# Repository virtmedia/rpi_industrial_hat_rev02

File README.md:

# rpi_industrial_hat_rev02
Raspberry Pi hat with industrial-style 2xDI+2xDQ+1W

## Features:
- power supply input 10-26 V with fuse protection, overvoltage protection and reverse polarity protection
- possible to set low voltage level eg. to protect 12V baterry from draining.
- 2 relays for outputs (both NO and NC contacts accesible)
- 2 optocouplers for inputs (can be used SMD or THT versions in 4-pin package)
- 3-pin connector for 1-Wire devices (eg. D18B20 thermometers)
- terminal blocks connectors
- UART conenctor
- I2C connector
- Domoticz and Home Assistant friendly

## Signals used from Raspberry Pi GPIO connector:
- GPIO04: 1-wire
- GPIO17: Relay #2
- GPIO18: Relay #1
- GPIO22: Input #1
- GPIO27: Input #2

Photo of the board (revision 01 with some small mistake, corrected in current revision):

I've included:
- Schematic in PDF
- Board visualisation in PDF
- Gerber files in .zip ready to be send to PCB manufacturer
- Eagle files

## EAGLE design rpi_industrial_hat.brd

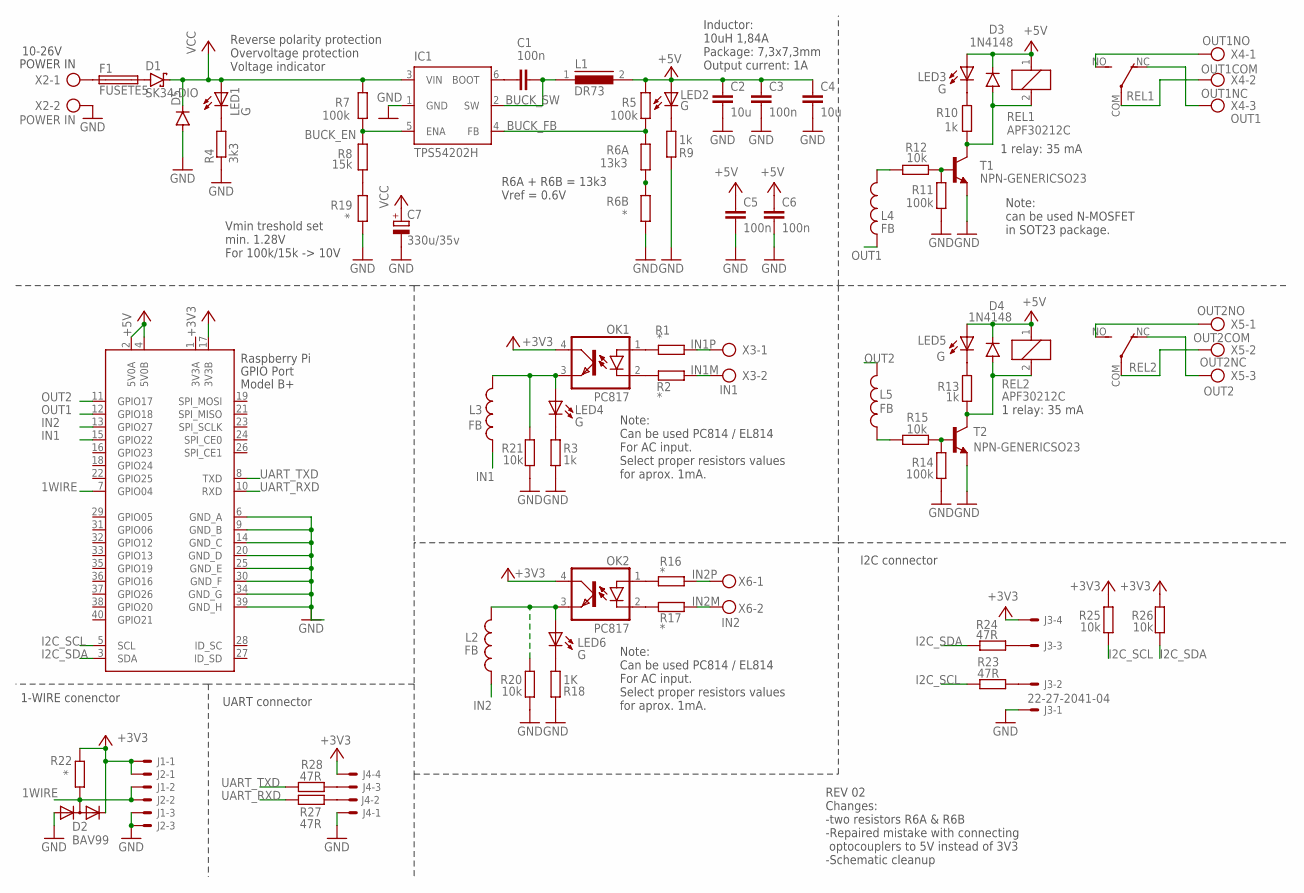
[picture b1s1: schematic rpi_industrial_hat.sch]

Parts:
C1, C3, C5, C6: 100n; C0603
C2, C4: 10u; C0805
C7: 330u/35v; E5-10,5
D1: SK34-DIO; SMC
D2: BAV99; SOT23
D3, D4: 1N4148; MINIMELF
D5: DIODE-DO214AA; DO214AA
F1: FUSETE5; TE5
IC1: TPS54202H; SOT23-6
J1, J2: 22-27-2031-03; 6410-03
J3, J4: 22-27-2041-04; 6410-04
L1: DR73
L2, L3, L4, L5: FB; 0603
LED1, LED2, LED3, LED4, LED5, LED6: G; CHIP-LED0603
OK1, OK2: PC817; DIL04
R1, R2, R16, R17: *; 0204/7/SMD
R3, R9, R10, R13: 1k; R0603
R4: 3k3; R0603
R5, R7, R11, R14: 100k; R0603
R6A: 13k3; R0603
R6B, R19, R22: *; R0603
R8: 15k; R0603
R12, R15, R20, R21, R25, R26: 10k; R0603
R18: 1K; R0603
R23, R24, R27, R28: 47R; R0603
REL1, REL2: APF30212C
T1, T2: NPN-GENERICSO23; SOT23
X1: RASPI_BOARD_B+#_E4P; RASPI_BOARD_B+_EDGES_4DRILL_PAD
X2: POWER IN; AK500/2
X3: IN1; AK500/2
X4: OUT1; AK500/3
X5: OUT2; AK500/3
X6: IN2; AK500/2

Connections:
1WIRE: D2.3 (K1A2), J1.2, J2.2, R22.1, X1.7 (GPIO04)
3V3A: X1.1 (3V3A)
+3V3: D2.2 (K2), J1.1, J2.1, J3.4, J4.4, OK1.4 (COL), OK2.4 (COL), R22.2, R25.1, R26.1, X1.17 (3V3B)
+5V: C2.1, C3.1, C4.1, C5.1, C6.1, D3.C, D4.C, L1.2, LED2.A, LED3.A, LED5.A, R5.2, REL1.1, REL2.1, X1.2 (5V0A), X1.4 (5V0B)
BUCK_EN: IC1.5 (ENA), R7.1, R8.2
BUCK_FB: IC1.4 (FB), R5.1, R6A.2
BUCK_SW: C1.2, IC1.2 (SW), L1.1
GND: C2.2, C3.2, C4.2, C5.2, C6.2, C7.-, D2.1 (A1), D5.A, IC1.1 (GND), J1.3, J2.3, J3.1, J4.1, R3.1, R4.1, R6B.1, R9.1, R11.1, R14.1, R18.1, R19.1, R20.1, R21.1, T1.2 (E), T2.2 (E), X1.6 (GND_A), X1.9 (GND_B), X1.14 (GND_C), X1.20 (GND_D), X1.25 (GND_E), X1.30 (GND_F), X1.34 (GND_G), X1.39 (GND_H), X2.2
I2C_SCL: R23.2, R25.2, X1.5 (SCL)
I2C_SDA: R24.2, R26.2, X1.3 (SDA)
IN1: L3.1, X1.15 (GPIO22)
IN1M: R2.1, X3.2
IN1P: R1.1, X3.1
IN1_: L3.2, LED4.A, OK1.3 (EMIT), R21.2
IN2: L2.1, X1.13 (GPIO27)
IN2M: R17.1, X6.2
IN2P: R16.1, X6.1
IN2_: L2.2, LED6.A, OK2.3 (EMIT), R20.2
unnamed: F1.1, X2.1
unnamed: D1.A, F1.2
unnamed: R8.1, R19.2
unnamed: J3.2, R23.1
unnamed: J3.3, R24.1
unnamed: OK1.1 (A), R1.2
unnamed: OK1.2 (C), R2.2
unnamed: J4.2, R27.1
unnamed: J4.3, R28.1
unnamed: LED4.C, R3.2
unnamed: C1.1, IC1.6 (BOOT)
unnamed: LED1.C, R4.2
unnamed: R6A.1, R6B.2
unnamed: D3.A, R10.1, REL1.2, T1.3 (C)
unnamed: LED2.C, R9.2
unnamed: LED3.C, R10.2
unnamed: R11.2, R12.1, T1.1 (B)
unnamed: D4.A, R13.1, REL2.2, T2.3 (C)
unnamed: LED5.C, R13.2
unnamed: R14.2, R15.1, T2.1 (B)
unnamed: OK2.1 (A), R16.2
unnamed: OK2.2 (C), R17.2
unnamed: LED6.C, R18.2
OUT1: L4.1, X1.12 (GPIO18)
OUT1COM: REL1.COM, X4.2
OUT1NC: REL1.NC (O), X4.3
OUT1NO: REL1.NO (S), X4.1
OUT1_: L4.2, R12.2
OUT2: L5.2, X1.11 (GPIO17)
OUT2COM: REL2.COM, X5.2
OUT2NC: REL2.NC (O), X5.3
OUT2NO: REL2.NO (S), X5.1
OUT2_: L5.1, R15.2
UART_RXD: R27.2, X1.10 (RXD)
UART_TXD: R28.2, X1.8 (TXD)
VCC: C7.+, D1.C, D5.C, IC1.3 (VIN), LED1.A, R7.2

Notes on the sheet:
POWER IN
Reverse polarity protection Overvoltage protection Voltage indicator
10-26V
1 relay: 35 mA
Inductor: 10uH 1,84A Package: 7,3x7,3mm Output current: 1A
R6A + R6B = 13k3 Vref = 0.6V
Vmin treshold set min. 1.28V For 100k/15k -> 10V
REV 02 Changes: -two resistors R6A & R6B -Repaired mistake with connecting optocouplers to 5V instead of 3V3 -Schematic cleanup
Note: can be used N-MOSFET in SOT23 package.
Note: Can be used PC814 / EL814 For AC input. Select proper resistors values for aprox. 1mA.
1-WIRE conenctor
UART connector
I2C connector

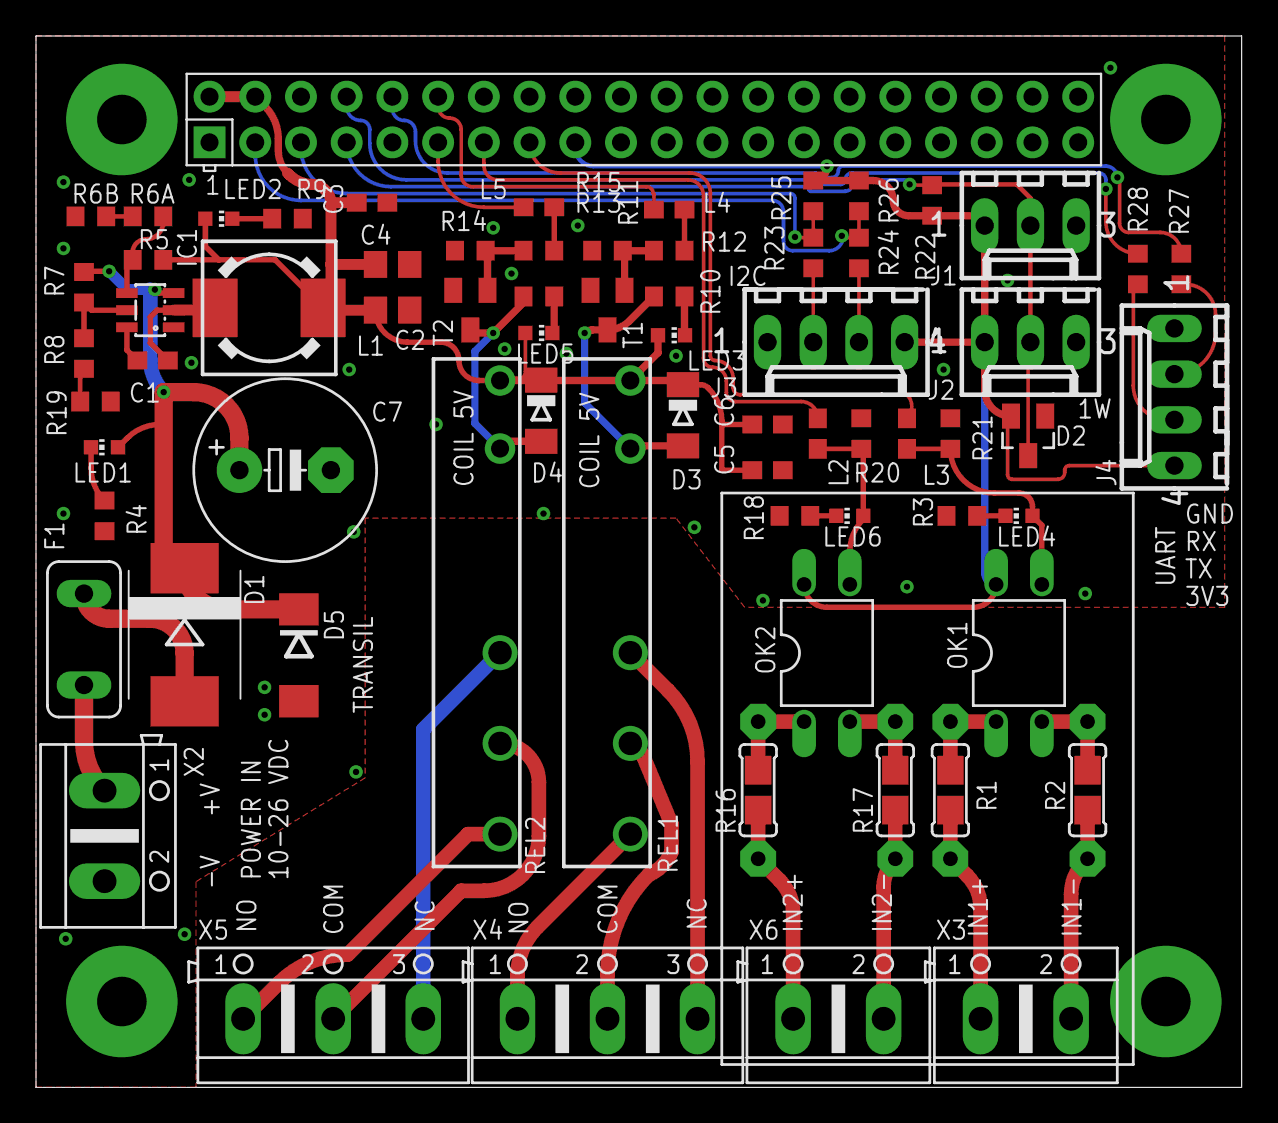
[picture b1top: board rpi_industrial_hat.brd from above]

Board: 2 copper layers, 67.0 x 58.4 mm, 70 parts (0 on the bottom side), 53 nets.

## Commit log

2022-12-27 Initial release.

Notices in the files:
parts and their libraries:
SparkFun: Licensing: CC v3.0 Share-Alike You are welcome to use this library for commercial purposes.
